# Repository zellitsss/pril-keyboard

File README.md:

Draft README for the Pril keyboard

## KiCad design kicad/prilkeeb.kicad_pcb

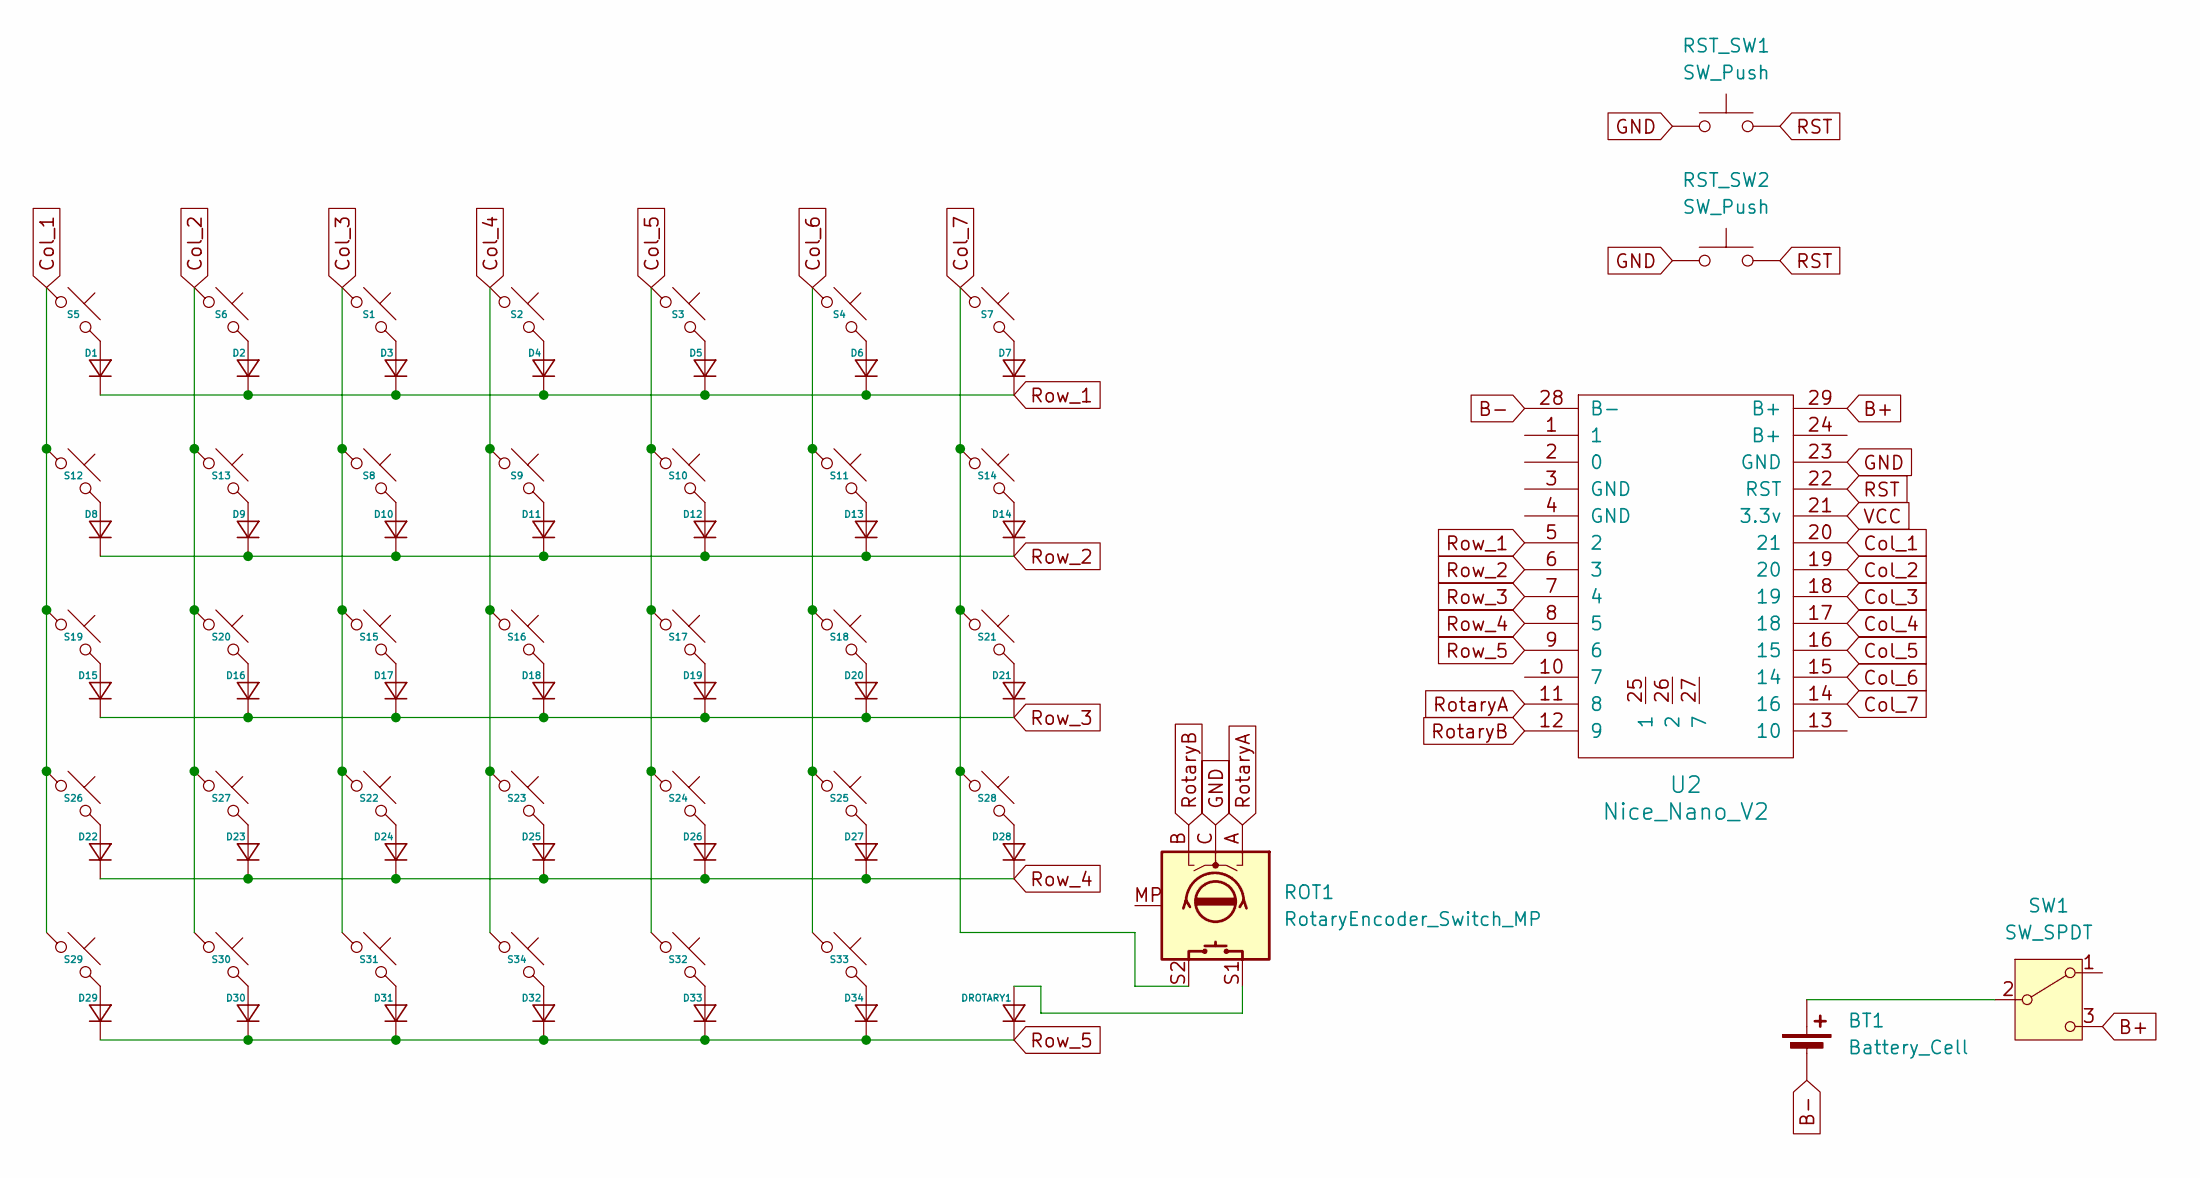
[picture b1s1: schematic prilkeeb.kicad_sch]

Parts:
BT1: Battery_Cell; Battery_pads_reversible
D1, D2, D3, D4, D5, D6, D7, D8, D9, D10, D11, D12, D13, D14, D15, D16, D17, D18, D19, D20, D21, D22, D23, D24, D25, D26, D27, D28, D29, D30, D31, D32, D33, D34: D_SMD_TH
DROTARY1: D_SMD_TH
ROT1: RotaryEncoder_Switch_MP; Encoder_EC11_MX_Jumpers_Reversible
RST_SW1, RST_SW2: SW_Push; Button_TL3342
S1: S3; SW_MX_HotSwap_PTH_double
S2: S4; SW_MX_HotSwap_PTH_double
S3: S5; SW_MX_HotSwap_PTH_double
S4: S6; SW_MX_HotSwap_PTH_double
S5: S1; SW_MX_HotSwap_PTH_double
S6: S2; SW_MX_HotSwap_PTH_double
S7: S7; SW_MX_HotSwap_PTH_double
S8: S10; SW_MX_HotSwap_PTH_double
S9: S11; SW_MX_HotSwap_PTH_double
S10: S12; SW_MX_HotSwap_PTH_double
S11: S13; SW_MX_HotSwap_PTH_double
S12: S8; SW_MX_HotSwap_PTH_double
S13: S9; SW_MX_HotSwap_PTH_double
S14: S14; SW_MX_HotSwap_PTH_double
S15: S17; SW_MX_HotSwap_PTH_double
S16: S18; SW_MX_HotSwap_PTH_double
S17: S19; SW_MX_HotSwap_PTH_double
S18: S20; SW_MX_HotSwap_PTH_double
S19: S15; SW_MX_HotSwap_PTH_double
S20: S16; SW_MX_HotSwap_PTH_double
S21: S21; SW_MX_HotSwap_PTH_double
S22: S24; SW_MX_HotSwap_PTH_double
S23: S25; SW_MX_HotSwap_PTH_double
S24: S26; SW_MX_HotSwap_PTH_double
S25: S27; SW_MX_HotSwap_PTH_double
S26: S22; SW_MX_HotSwap_PTH_double
S27: S23; SW_MX_HotSwap_PTH_double
S28: S28; SW_MX_HotSwap_PTH_double
S29: S29; SW_MX_HotSwap_PTH_double
S30: S30; SW_MX_HotSwap_PTH_double
S31: S31; SW_MX_HotSwap_PTH_double
S32: S33; SW_MX_HotSwap_PTH_double
S33: S34; SW_MX_HotSwap_PTH_double
S34: S32; SW_MX_HotSwap_PTH_double
SW1: SW_SPDT; power_switch_padreverse
U2: Nice_Nano_V2

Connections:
B+: SW1.3 (C), U2.29 (B+)
B-: BT1.2 (-), U2.28 (B-)
Col_1: S5.1, S12.1, S19.1, S26.1, S29.1, U2.20 (21)
Col_2: S6.1, S13.1, S20.1, S27.1, S30.1, U2.19 (20)
Col_3: S1.1, S8.1, S15.1, S22.1, S31.1, U2.18 (19)
Col_4: S2.1, S9.1, S16.1, S23.1, S34.1, U2.17 (18)
Col_5: S3.1, S10.1, S17.1, S24.1, S32.1, U2.16 (15)
Col_6: S4.1, S11.1, S18.1, S25.1, S33.1, U2.15 (14)
Col_7: ROT1.S2, S7.1, S14.1, S21.1, S28.1, U2.14 (16)
GND: ROT1.C, RST_SW1.1, RST_SW2.1, U2.23 (GND)
unnamed: BT1.1 (+), SW1.2 (B)
unnamed: D1.2 (A), S5.2
unnamed: D2.2 (A), S6.2
unnamed: D3.2 (A), S1.2
unnamed: D4.2 (A), S2.2
unnamed: D5.2 (A), S3.2
unnamed: D6.2 (A), S4.2
unnamed: D7.2 (A), S7.2
unnamed: D8.2 (A), S12.2
unnamed: D9.2 (A), S13.2
unnamed: D10.2 (A), S8.2
unnamed: D11.2 (A), S9.2
unnamed: D12.2 (A), S10.2
unnamed: D13.2 (A), S11.2
unnamed: D14.2 (A), S14.2
unnamed: D15.2 (A), S19.2
unnamed: D16.2 (A), S20.2
unnamed: D17.2 (A), S15.2
unnamed: D18.2 (A), S16.2
unnamed: D19.2 (A), S17.2
unnamed: D20.2 (A), S18.2
unnamed: D21.2 (A), S21.2
unnamed: D22.2 (A), S26.2
unnamed: D23.2 (A), S27.2
unnamed: D24.2 (A), S22.2
unnamed: D25.2 (A), S23.2
unnamed: D26.2 (A), S24.2
unnamed: D27.2 (A), S25.2
unnamed: D28.2 (A), S28.2
unnamed: D29.2 (A), S29.2
unnamed: D30.2 (A), S30.2
unnamed: D31.2 (A), S31.2
unnamed: D32.2 (A), S34.2
unnamed: D33.2 (A), S32.2
unnamed: D34.2 (A), S33.2
unnamed: DROTARY1.2 (A), ROT1.S1
RST: RST_SW1.2, RST_SW2.2, U2.22 (RST)
RotaryA: ROT1.A, U2.11 (8)
RotaryB: ROT1.B, U2.12 (9)
Row_1: D1.1 (K), D2.1 (K), D3.1 (K), D4.1 (K), D5.1 (K), D6.1 (K), D7.1 (K), U2.5 (2)
Row_2: D8.1 (K), D9.1 (K), D10.1 (K), D11.1 (K), D12.1 (K), D13.1 (K), D14.1 (K), U2.6 (3)
Row_3: D15.1 (K), D16.1 (K), D17.1 (K), D18.1 (K), D19.1 (K), D20.1 (K), D21.1 (K), U2.7 (4)
Row_4: D22.1 (K), D23.1 (K), D24.1 (K), D25.1 (K), D26.1 (K), D27.1 (K), D28.1 (K), U2.8 (5)
Row_5: D29.1 (K), D30.1 (K), D31.1 (K), D32.1 (K), D33.1 (K), D34.1 (K), DROTARY1.1 (K), U2.9 (6)
VCC: U2.21 (3.3v)

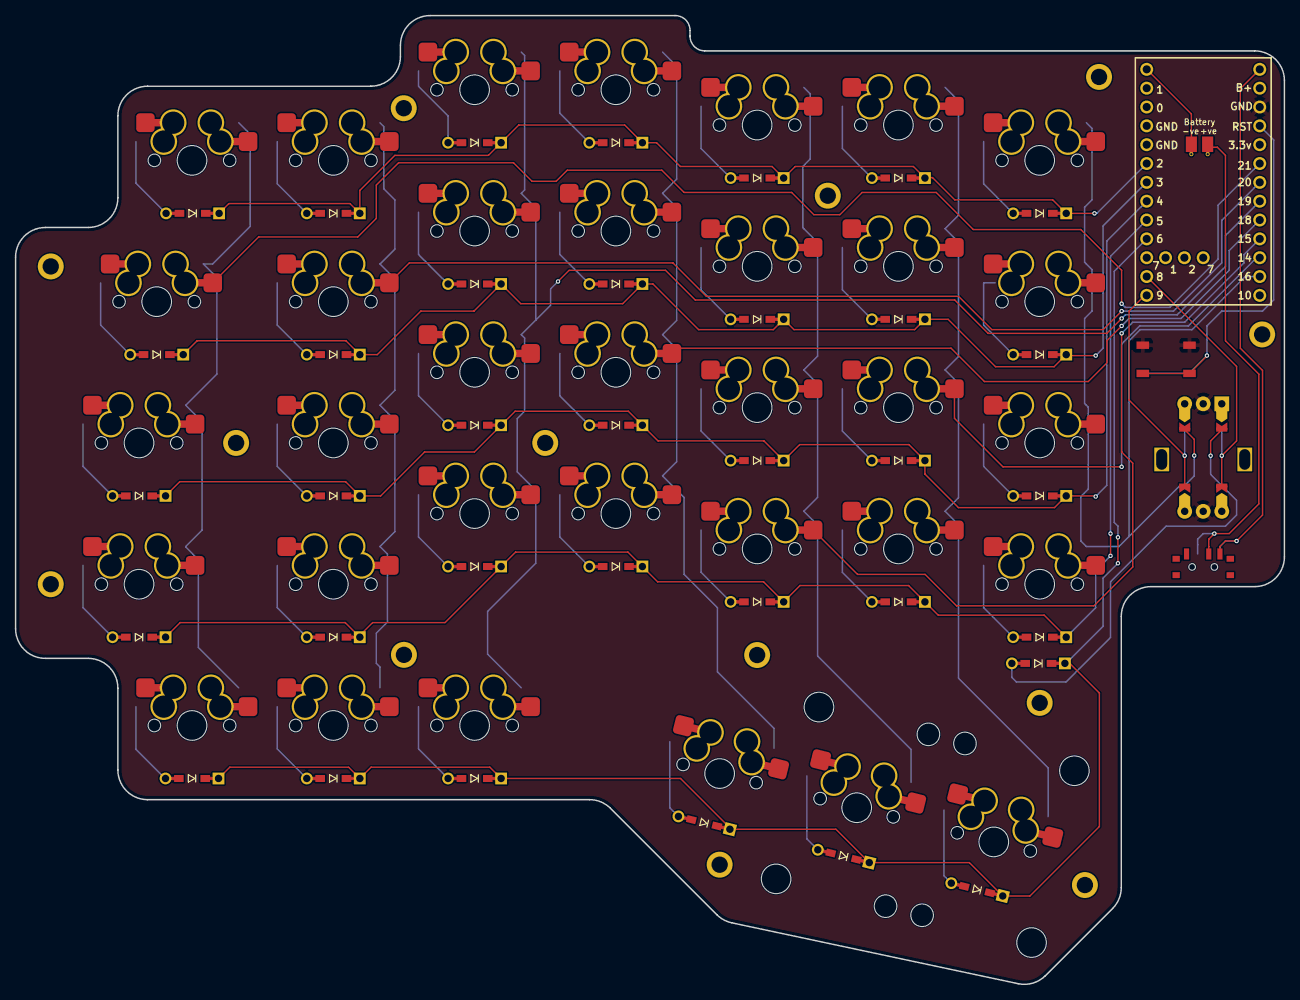
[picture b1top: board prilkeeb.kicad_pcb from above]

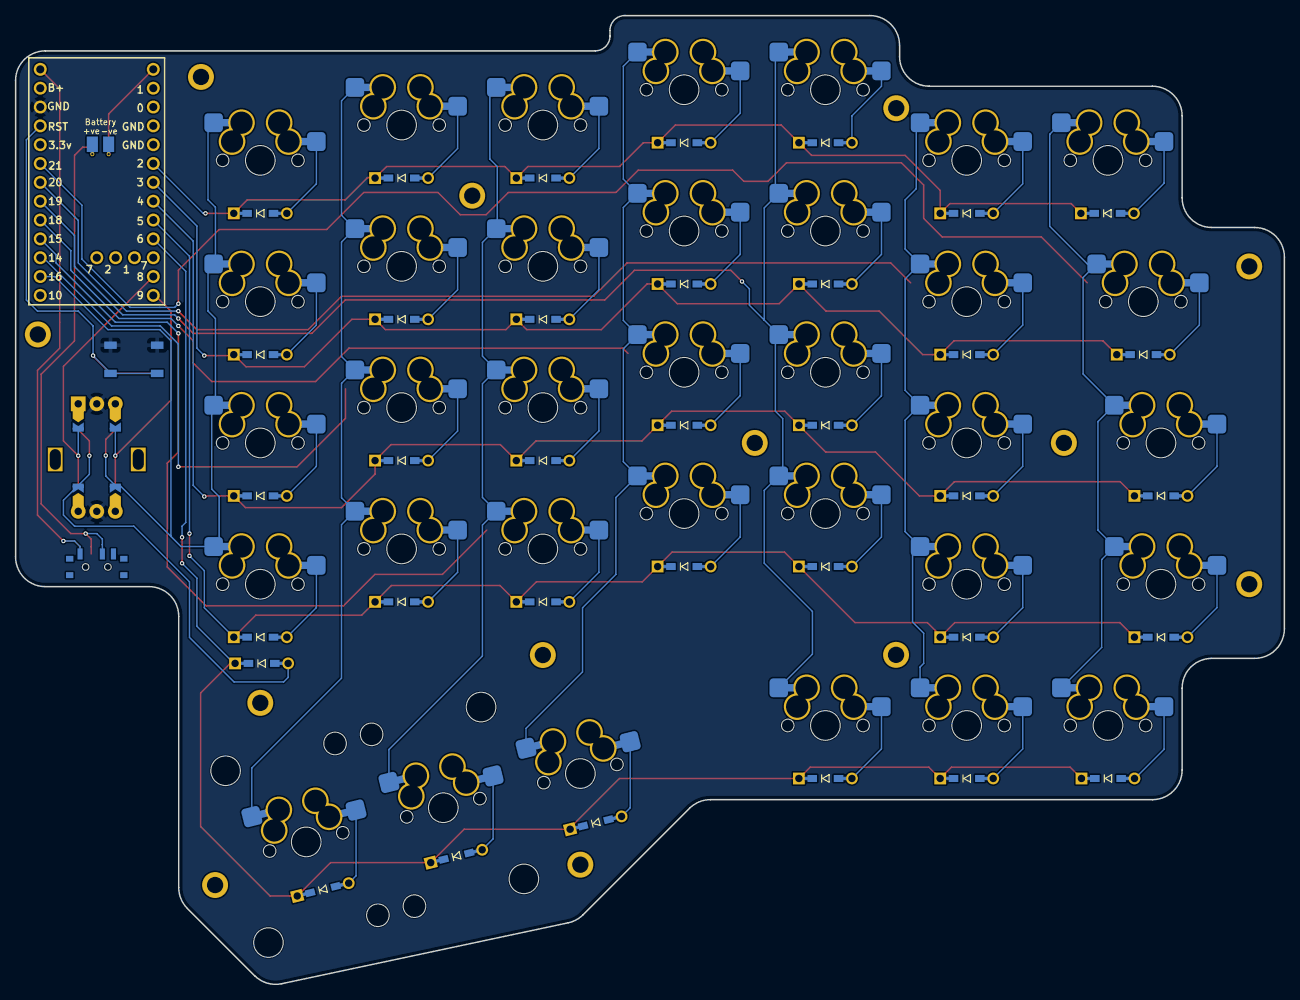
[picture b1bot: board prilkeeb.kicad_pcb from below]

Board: 2 copper layers, 171.1 x 130.6 mm, 89 parts (36 on the bottom side), 54 nets.

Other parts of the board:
 : Stabilizer_MX_2.00u
 #2: Stabilizer_MX_2.00u
Ref**: Val**; M2_hole_3.5mm
Ref**#2, Ref**#3, Ref**#4, Ref**#5, Ref**#6, Ref**#7, Ref**#8, Ref**#9, Ref**#10, Ref**#11, Ref**#12: Val**; M2_hole_3.5mm

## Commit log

2026-01-10 First init
2026-01-10 Add kicad project
2026-01-10 Add unfinished layout
2026-01-10 Update layout
2026-01-10 Update placement and basice routing
2026-01-10 Update project name
2026-01-11 Acceptable tracks
2026-01-11 Add gitignore
2026-01-12 Nearly finish the routing
2026-01-14 Routing
2026-01-16 Update gitignore
2026-01-16 Untrack files
2026-01-16 Update design
2026-01-16 Update pcb
2026-01-17 Update ignore
2026-01-19 Update MCU position
2026-01-19 Adapt new design
2026-01-19 Design with case
2026-01-19 Design with holes
2026-01-21 Add hole
2026-01-24 Design checkpoint
2026-01-25 Basic routing
2026-01-25 Routing cont
2026-01-26 Update components
2026-01-26 Update edgecut
2026-01-26 Update diode type
2026-01-26 Mounting holes
2026-01-26 Fix mounting holes
2026-01-27 Mounting holes design
